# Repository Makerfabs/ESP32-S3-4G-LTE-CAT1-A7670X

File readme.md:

# ESP32-S3-Parallel-TFT-with-Touch-1.9inch

```
/* 
    Version:      V1.0
    Author:       Vincent
    Create Date:  2023/8/22
*/
```

# Makerfabs

[Makerfabs home page](https://www.makerfabs.com/)

[Makerfabs Wiki](https://wiki.makerfabs.com/)

## Intruduce

Product Link:

Wiki Link : 

## Features

- Controller: ESP32-S3
- Wireless: WiFi& Bluetooth 5.0
- Arduino support
- MicroPython support: Yes
- Operation temperature: -40℃ to +85℃
- USB: USB Native, Type-C
- Power Supply: USB Type-C 5.0V(4.0V~5.25V); 3.7V Lipo battery

# Usage

All supporting information, such as the AT instructions and other official documents are in the A76XX Manual.zip.

## Complier Option

- Use type-c use cable connect USB-TTL to PC.
- Select "ESP32-S3 DEV Module"
- Select PSRAM "OPI PSRAM"

## Example

at_command_demo.ino

Serial port transparent transmission demo.
Can be used to test AT Commands.

## AT Commands

### AT+CSQ

Query signal quality

```
AT+CSQ
+CSQ: 28,99

OK

```

### AT+SIMCOMATI

Example Query module information

```
AT+SIMCOMATI
Manufacturer: INCORPORATED
Model: A7670SA-FASE
Revision: A011B04A7670M7_F
A7670M7_B04V02_220927
QCN:
IMEI: 869731059057646
MEID:
+GCAP: +CGSM,+FCLASS,+DS
DeviceInfo:

OK

```

### AT+COPS

Operator selection

```
AT+COPS?
+COPS: 0,2,"46000",7

OK

```

### AT+CICCID

Read ICCID from SIM card

```
AT+CICCID
+ICCID: 898607E0102250030751

OK

```

### AT+CBC

Read the voltage value of the power supply

```
AT+CBC
+CBC: 4.167V

OK

```

## TTS Test

```
AT+CTTSPARAM=? 
AT+CTTSPARAM=1,3,0,1,1 
AT+CTTSPARAM?
AT+CTTS=1,"6B228FCE4F7F75288BED97F3540862107CFB7EDF" 
AT+CTTS=2,"Hi, Makerfabs"

```

## LBS Test

```
AT+CLBS=? 
AT+SIMCOMATI
AT+SIMEI=xxxxx 
AT+CLBS=2 
AT+CLBS=1
```

## Make a call

```
ATD<phone_number>;
AT+COUTGAIN=?
AT+COUTGAIN=5
AT+CHUP 
```
## TCP test

```
AT+CIPMODE=1
AT+NETOPEN
AT+CIPOPEN=0,"TCP","122.114.122.174",39348
Hi,Makerfabs
AT+CIPCLOSE=0
AT+NETCLOSE
```
## LBS Test

```
AT+CLBS=? 
AT+SIMCOMATI
AT+SIMEI=xxxxx 
AT+CLBS=2 
AT+CLBS=1
```
## HTTP Test

```
AT+HTTPINIT
AT+HTTPPARA="URL","http:www.makerfabs.com"
AT+HTTPACTION=0
AT+HTTPHEAD
AT+HTTPREAD=0,500
AT+HTTPTERM
```

## MQTT Test

```
AT+CMQTTSTART
AT+CMQTTACCQ=0,"client test0"
AT+CMQTTWILLTOPIC=0,10
AT+CMQTTWILLMSG=0,6,1
AT+CMQTTCONNECT=0,"tcp://test.mosquitto.org:1883",60,1
AT+CMQTTSUB=0,9,1
AT+CMQTTTOPIC=0,9
AT+CMQTTPAYLOAD=0,60
```

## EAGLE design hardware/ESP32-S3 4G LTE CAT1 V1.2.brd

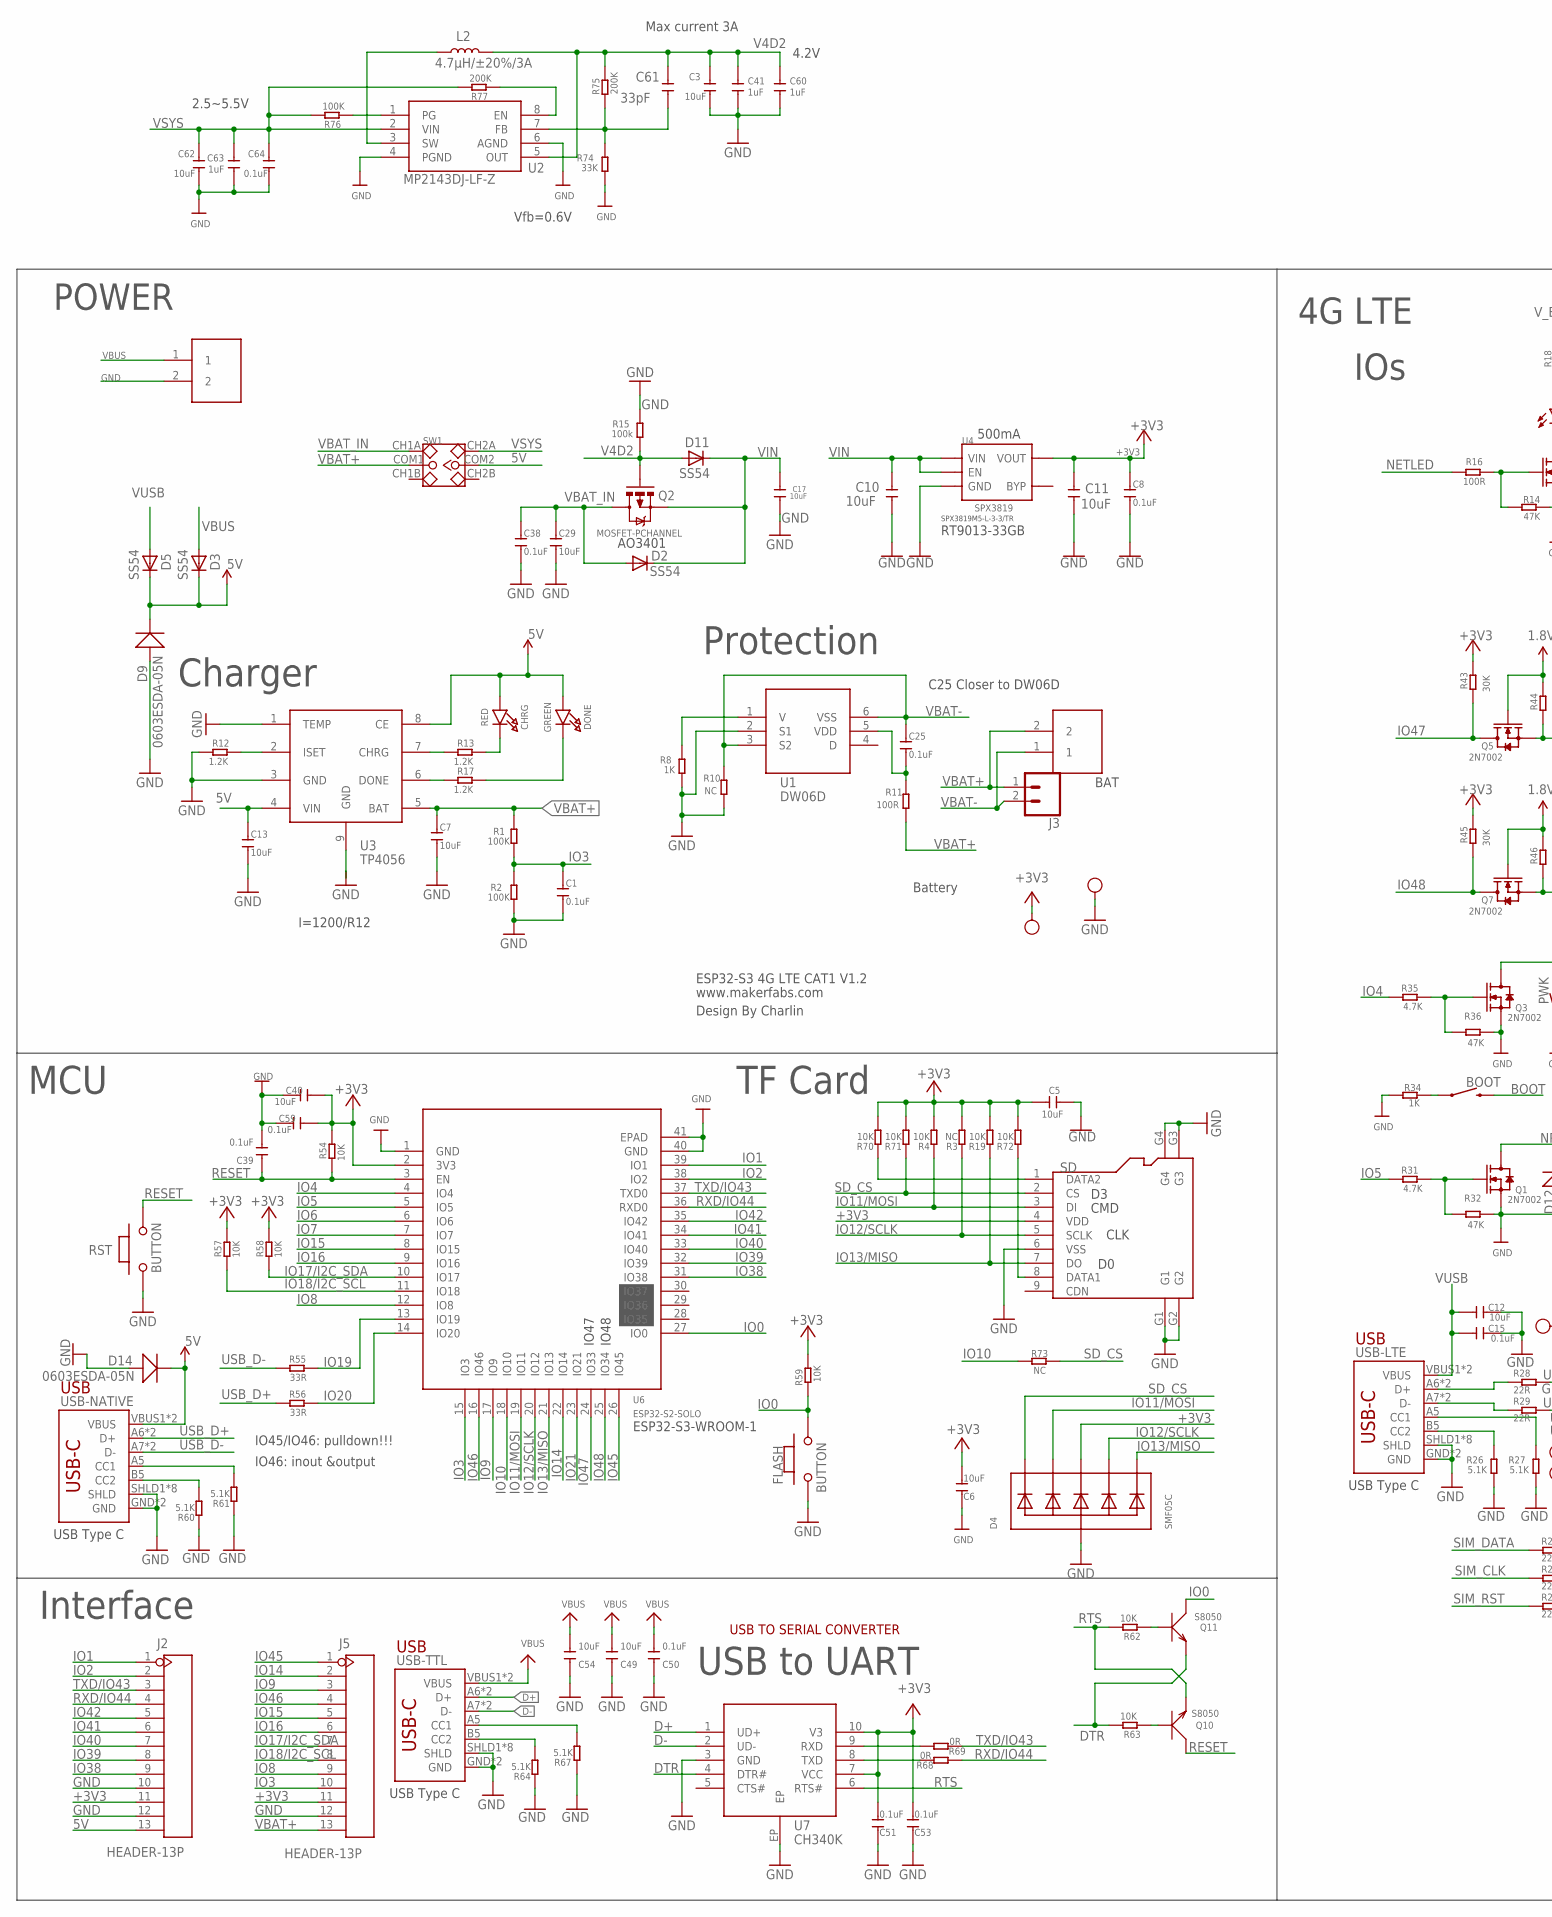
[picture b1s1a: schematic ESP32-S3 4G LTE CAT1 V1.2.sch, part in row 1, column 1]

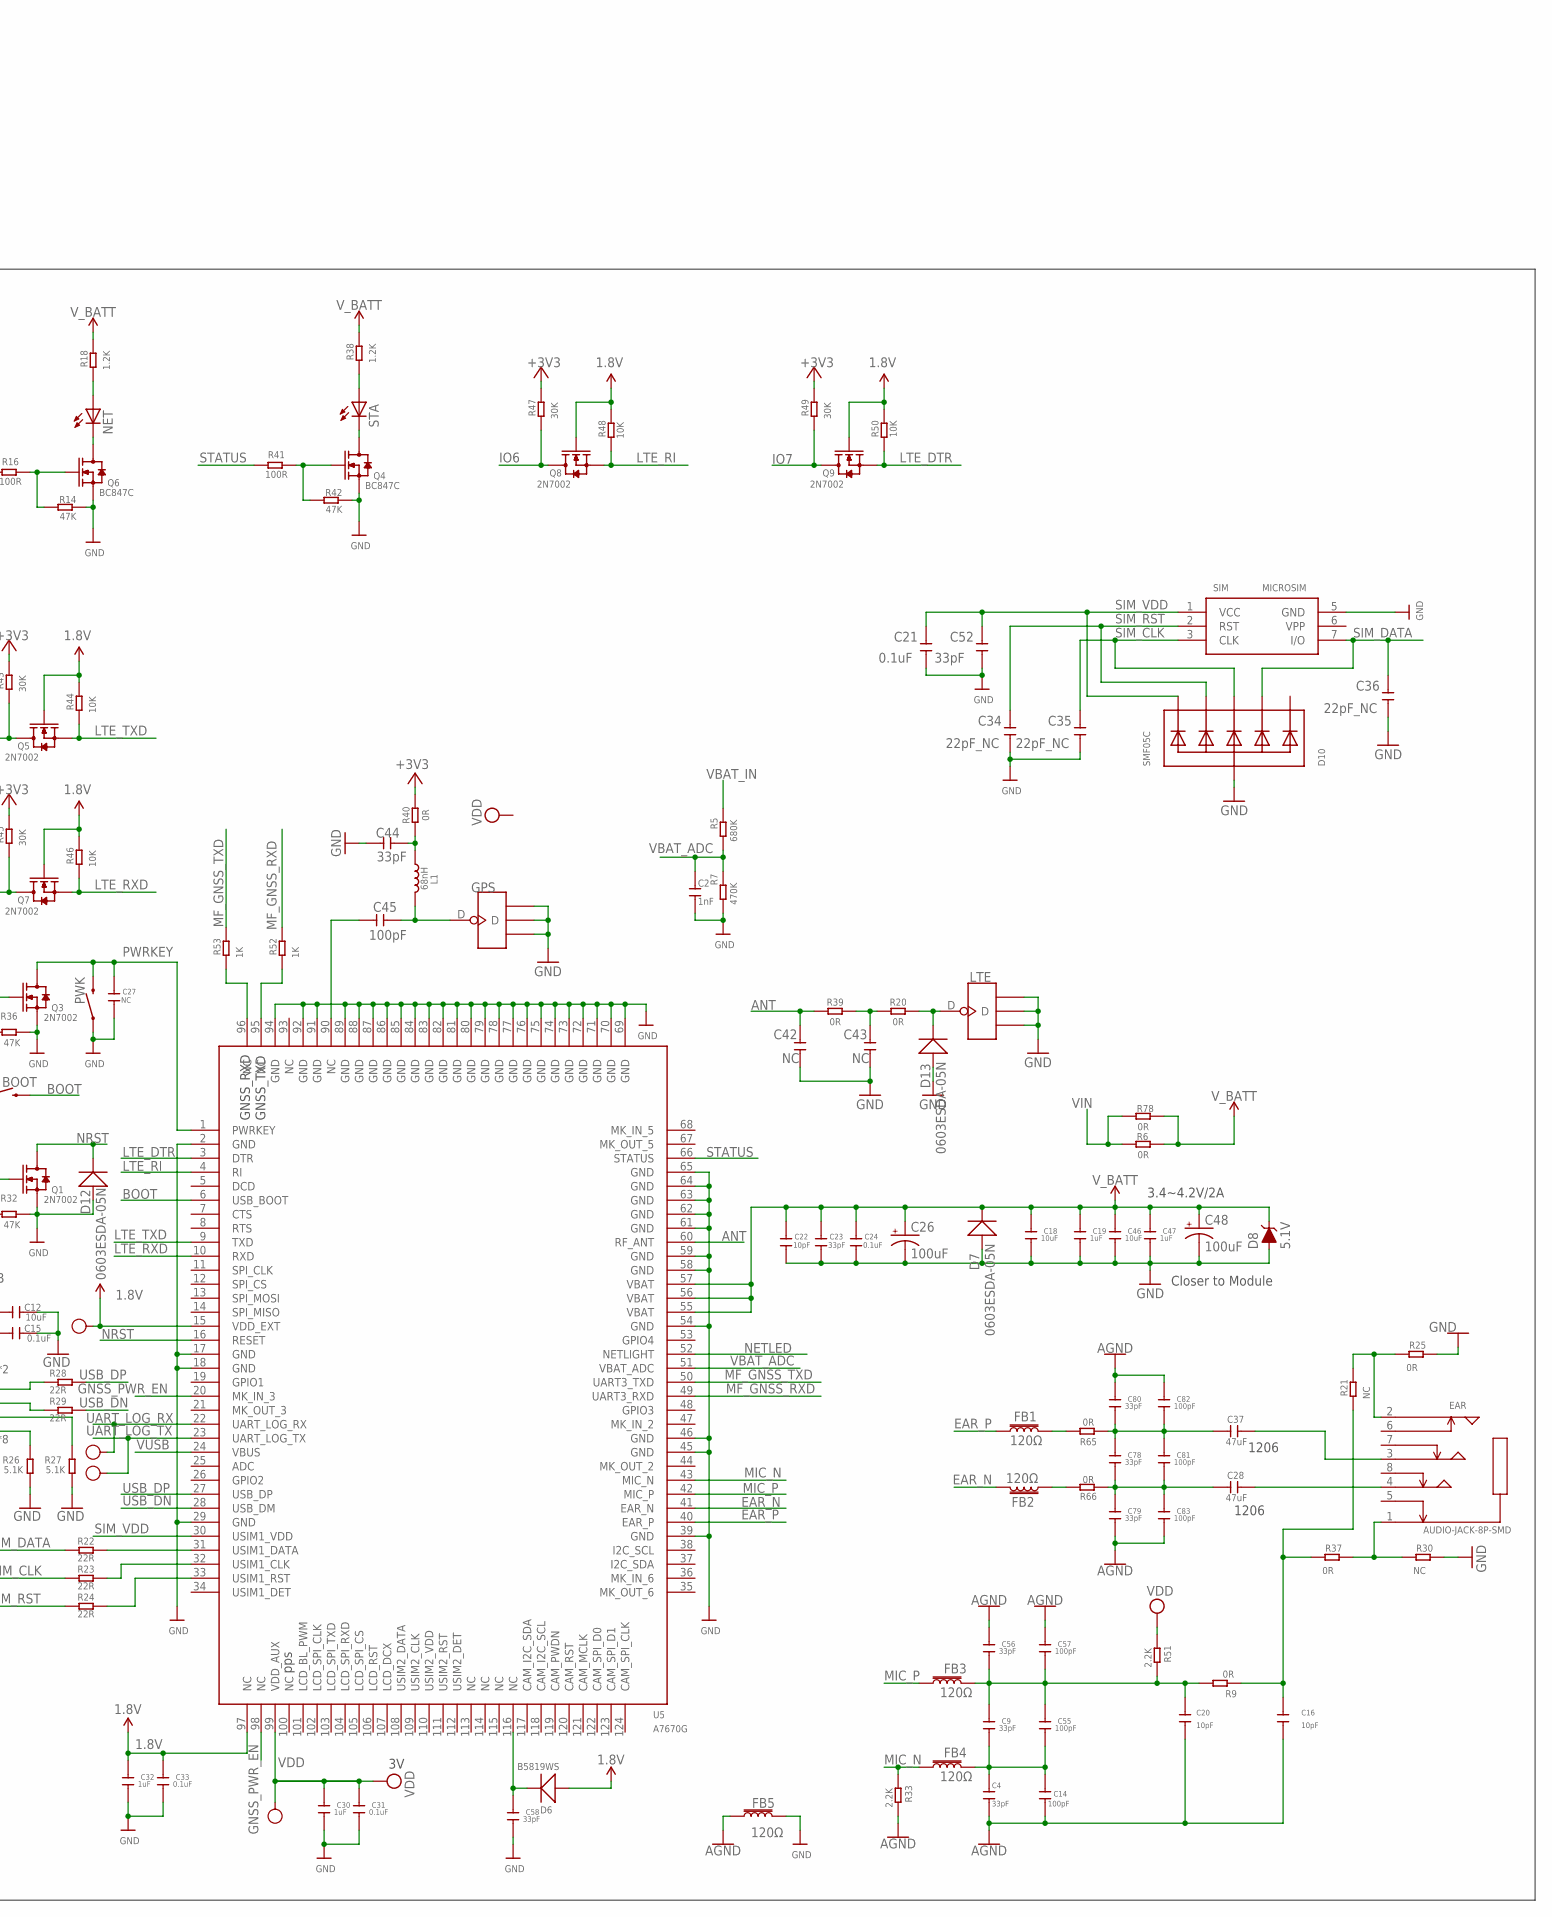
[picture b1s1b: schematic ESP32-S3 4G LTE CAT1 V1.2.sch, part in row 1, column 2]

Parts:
1V8, 3V, 3V3: TEST-POINT'4545'; TP-D45MIL; PARTNO DNP
BAT: PH2.0-2P-90-DIP
BOOT: MOMENTARY-SWITCH-SPST-SMD-6.0X3.5MM; TACTILE_SWITCH_SMD_6.0X3.5MM
C1, C8, C15, C21, C24, C25, C31, C33, C38, C64: 0.1uF; 0603
C2: 1nF; 0603
C3, C7, C10, C11, C12, C13, C17, C18, C29, C46, C62: 10uF; 0603
C4, C9, C23, C44, C52, C56, C58, C61, C78, C79, C80: 33pF; 0603
C5, C6, C40, C49, C54: 10uF; DISCRETE_C0603
C14, C45, C55, C57, C81, C82, C83: 100pF; 0603
C16, C20, C22: 10pF; 0603
C19, C30, C32, C41, C47, C60, C63: 1uF; 0603
C26, C48: 100uF; EIA3528
C27, C42, C43: NC; 0603
C28, C37: 47uF; DISCRETE_C1206
C34, C35, C36: 22pF_NC; 0603
C39, C50, C51, C53, C59: 0.1uF; DISCRETE_C0603
CHRG: RED; CHIPLED_0805_NOOUTLINE
D2, D3, D5, D11: SS54; DO-214AC
D4, D10: SMF05C; SOT363
D6: B5819WS; SOD323
D7, D9, D12, D13, D14: 0603ESDA-05N; DISCRETE_SOD523
D8: 5.1V; SOD-323
DONE: GREEN; CHIPLED_0805_NOOUTLINE
EAR: AUDIO-JACK-8P-SMD; AUDIO8P-SMD-3.5-14.5X6.1X4.0MM
FB1, FB2, FB3, FB4, FB5: 120Ω; 0603
FLASH: BUTTON; 157SW
GND: TEST-POINT'4545'; TP-D45MIL; PARTNO DNP
GPS: ANTENNA-U-FL; 4P-U-FL
J1: PH2.0-2P-90-DIP
J2, J5: HEADER-13P; 13P-2.54
J3: CONN_02LOCK; 1X02_LOCK
L1: 68nH; L0603
L2: 4.7µH/±20%/3A; SRN6045
LTE: ANTENNA-U-FL; 4P-U-FL
NET: NET; CHIP-LED0805
PWK: MOMENTARY-SWITCH-SPST-SMD-6.0X3.5MM; TACTILE_SWITCH_SMD_6.0X3.5MM
Q1, Q3, Q5, Q7, Q8, Q9: 2N7002; SOT23
Q2: MOSFET-PCHANNEL; SOT23-3
Q4, Q6: BC847C; SOT23
Q10, Q11: S8050; SOT23
R1, R2, R76: 100K; R0603
R3: NC; DISCRETE_R0603
R4, R19, R70, R71, R72: 10K; DISCRETE_R0603
R5: 680K; R0603
R6, R9, R20, R25, R37, R39, R40, R65, R66, R68, R69, R78: 0R; R0603
R7: 470K; R0603
R8, R34, R52, R53: 1K; R0603
R10, R21, R30, R73: NC; R0603
R11, R16, R41: 100R; R0603
R12, R13, R17, R18, R38: 1.2K; R0603
R14, R32, R36, R42: 47K; R0603
R15: 100k; R0603
R22, R23, R24, R28, R29: 22R; R0603
R26, R27: 5.1K; R0603
R31, R35: 4.7K; R0603
R33, R51: 2.2K; R0603
R43, R45, R47, R49: 30K; R0603
R44, R46, R48, R50, R54, R57, R58, R59, R62, R63: 10K; R0603
R55, R56: 33R; R0603
R60, R61, R64, R67: 5.1K; DISCRETE_R0603
R74: 33K; R0603
R75, R77: 200K; R0603
RST: BUTTON; 157SW
RX: TEST-POINT'4545'; TP-D45MIL; PARTNO DNP
SD: HOLDER-MICROSD-9P; 9P-SMD-W/-RING
SIM: MICROSIM
STA: NET; CHIP-LED0805
SW1: SWITCH-2CH-6P; 6P-2CH-2.54-7.6X3.0
TX: TEST-POINT'4545'; TP-D45MIL; PARTNO DNP
U1: DW06D; SOT-23-6
U2: MP2143DJ-LF-Z; TSOT23-8
U3: TP4056; SOP8-1.27P
U4: SPX3819; SOT23-5
U5: A7670G
U6: ESP32­S2­SOLO; ESP32-­S2-­SOLO
U7: CH340K; ESOP-10-EP-150MIL
USB-LTE: USB_C5; USB-C-16P-5
USB-NATIVE: USB_C5; USB-C-16P-5
USB-TTL: USB_C5; USB-C-16P-5

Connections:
1.8V: 1V8.T, C32.2, C33.2, D6.+, Q5.1 (G), Q7.1 (G), Q8.1 (G), Q9.1 (G), R44.2, R46.2, R48.2, R50.2, U5.15 (VDD_EXT), U5.97 (NC)
5V: C13.1, CHRG.A, D3.C, D5.C, D9.-, D14.-, DONE.A, J2.13, SW1.COM2, U3.4 (VIN), U3.8 (CE), USB-NATIVE.VBUS1 (VBUS), USB-NATIVE.VBUS2 (VBUS)
+3V3: 3V3.T, C5.2, C6.2, C8.1, C11.2, C40.2, C51.2, C53.2, C59.2, D4.4 (C3), J2.11, J5.11, R3.2, R4.2, R19.2, R40.2, R43.2, R45.2, R47.2, R49.2, R54.2, R57.2, R58.2, R59.2, R70.2, R71.2, R72.2, SD.4 (VDD), U4.5 (VOUT), U6.2 (3V3), U7.7 (VCC), U7.10 (V3)
AGND: C4.1, C14.1, C16.1, C20.1, C56.2, C57.2, C79.1, C80.2, C82.2, C83.1, FB5.1, R33.2
ANT: C42.2, R39.1, U5.60 (RF_ANT)
BOOT: BOOT.2, U5.6 (USB_BOOT)
D+: U7.1 (UD+), USB-TTL.A6 (D+), USB-TTL.B6 (D+)
D-: U7.2 (UD-), USB-TTL.A7 (D-), USB-TTL.B7 (D-)
DONE: R17.2, U3.6 (DONE)
DTR: Q11.2 (E), R63.2, U7.4 (DTR#)
EAR_N: FB2.2, U5.41 (EAR_N)
EAR_P: FB1.1, U5.40 (EAR_P)
GND: C1.2, C2.2, C3.1, C5.1, C6.1, C7.2, C8.2, C10.1, C11.1, C12.2, C13.2, C15.2, C17.1, C18.1, C19.1, C21.1, C22.1, C23.1, C24.1, C26.C (-), C27.1, C29.2, C30.1, C31.1, C32.1, C33.1, C34.1, C35.1, C36.1, C38.2, C39.2, C40.1, C41.1, C42.1, C43.1, C44.2, C46.1, C47.1, C48.C (-), C49.1, C50.1, C51.1, C52.1, C53.1, C54.1, C58.1, C59.1, C60.1, C62.1, C63.1, C64.1, D4.2 (A), D7.+, D8.A, D9.+, D10.2 (A), D12.+, D13.+, D14.+, FB5.2, FLASH.1, GND.T, GPS.GND1, GPS.GND2, GPS.GND3, J1.2, J2.10, J2.12, J5.12, LTE.GND1, LTE.GND2, LTE.GND3, PWK.1, Q1.2 (S), Q3.2 (S), Q4.2 (S), Q6.2 (S), R2.1, R7.1, R8.1, R10.1, R12.2, R14.1, R15.2, R25.2, R26.1, R27.1, R30.2, R32.1, R34.2, R36.1, R42.1, R60.1, R61.1, R64.1, R67.1, R74.1, RST.1, SD.6 (VSS), SD.G1, SD.G2, SD.G3, SD.G4, SIM.5 (GND), U1.2 (S1), U2.4 (PGND), U2.6 (AGND), U3.1 (TEMP), U3.3 (GND), U3.9 (GND), U4.2 (GND), U5.2 (GND), U5.17 (GND), U5.18 (GND), U5.29 (GND), U5.39 (GND), U5.45 (GND), U5.46 (GND), U5.54 (GND), U5.58 (GND), U5.59 (GND), U5.61 (GND), U5.62 (GND), U5.63 (GND), U5.64 (GND), U5.65 (GND), U5.69 (GND), U5.70 (GND), U5.71 (GND), U5.72 (GND), U5.73 (GND), U5.74 (GND), U5.75 (GND), U5.76 (GND), U5.77 (GND), U5.78 (GND), U5.79 (GND), U5.80 (GND), U5.81 (GND), U5.82 (GND), U5.83 (GND), U5.84 (GND), U5.85 (GND), U5.86 (GND), U5.87 (GND), U5.88 (GND), U5.89 (GND), U5.91 (GND), U5.92 (GND), U5.94 (GND), U6.1 (GND), U6.40 (GND), U6.41 (EPAD), U7.3 (GND), U7.EP, USB-LTE.GND, USB-LTE.GND2 (GND), USB-LTE.SHLD1 (SHLD), USB-LTE.SHLD2 (SHLD), USB-LTE.SHLD3 (SHLD), USB-LTE.SHLD4 (SHLD), USB-LTE.SHLD5 (SHLD), USB-LTE.SHLD6 (SHLD), USB-LTE.SHLD7 (SHLD), USB-LTE.SHLD8 (SHLD), USB-NATIVE.GND, USB-NATIVE.GND2 (GND), USB-NATIVE.SHLD1 (SHLD), USB-NATIVE.SHLD2 (SHLD), USB-NATIVE.SHLD3 (SHLD), USB-NATIVE.SHLD4 (SHLD), USB-NATIVE.SHLD5 (SHLD), USB-NATIVE.SHLD6 (SHLD), USB-NATIVE.SHLD7 (SHLD), USB-NATIVE.SHLD8 (SHLD), USB-TTL.GND, USB-TTL.GND2 (GND), USB-TTL.SHLD1 (SHLD), USB-TTL.SHLD2 (SHLD), USB-TTL.SHLD3 (SHLD), USB-TTL.SHLD4 (SHLD), USB-TTL.SHLD5 (SHLD), USB-TTL.SHLD6 (SHLD), USB-TTL.SHLD7 (SHLD), USB-TTL.SHLD8 (SHLD)
GNSS_PWR_EN: U5.20 (MK_IN_3), U5.98 (NC)
IO0: FLASH.2, Q11.3 (C), R59.1, U6.27 (IO0)
IO1: J2.1, U6.39 (IO1)
IO2: J2.2, U6.38 (IO2)
IO3: C1.1, J5.10, R1.1, R2.2, U6.15 (IO3)
IO4: R35.2, U6.4 (IO4)
IO5: R31.2, U6.5 (IO5)
IO6: Q8.3 (D), R47.1, U6.6 (IO6)
IO7: Q9.3 (D), R49.1, U6.7 (IO7)
IO8: J5.9, U6.12 (IO8)
IO9: J5.3, U6.17 (IO9)
IO10: R73.1, U6.18 (IO10)
IO11/MOSI: D4.3 (C2), R4.1, SD.3 (DI), U6.19 (IO11)
IO12/SCLK: D4.5 (C4), R3.1, SD.5 (SCLK), U6.20 (IO12)
IO13/MISO: D4.6 (C5), R19.1, SD.7 (DO), U6.21 (IO13)
IO14: J5.2, U6.22 (IO14)
IO15: J5.5, U6.8 (IO15)
IO16: J5.6, U6.9 (IO16)
IO17/I2C_SDA: J5.7, R58.1, U6.10 (IO17)
IO18/I2C_SCL: J5.8, R57.1, U6.11 (IO18)
IO19: R55.2, U6.13 (IO19)
IO20: R56.2, U6.14 (IO20)
IO21: U6.23 (IO21)
IO38: J2.9, U6.31 (IO38)
IO39: J2.8, U6.32 (IO39)
IO40: J2.7, U6.33 (IO40)
IO41: J2.6, U6.34 (IO41)
IO42: J2.5, U6.35 (IO42)
IO45: J5.1, U6.26 (IO45)
IO46: J5.4, U6.16 (IO46)
IO47: Q5.3 (D), R43.1, U6.24 (IO33)
IO48: Q7.3 (D), R45.1, U6.25 (IO34)
ISET: R12.1, U3.2 (ISET)
LTE_DTR: Q9.2 (S), R50.1, U5.3 (DTR)
LTE_RI: Q8.2 (S), R48.1, U5.4 (RI)
LTE_RXD: Q7.2 (S), R46.1, U5.10 (RXD)
LTE_TXD: Q5.2 (S), R44.1, U5.9 (TXD)
MF_GNSS_RXD: R52.2, U5.49 (UART3_RXD)
MF_GNSS_TXD: R53.2, U5.50 (UART3_TXD)
MIC_N: FB4.1, R33.1, U5.43 (MIC_N)
MIC_P: FB3.1, U5.42 (MIC_P)
unnamed: NET.C, Q6.3 (D)
unnamed: CHRG.C, R13.1
unnamed: D13.-, LTE.D, R20.2
unnamed: Q4.1 (G), R41.1, R42.2
unnamed: Q6.1 (G), R14.2, R16.1
unnamed: NET.A, R18.1
unnamed: R70.1, SD.1 (DATA2)
unnamed: BOOT.1, R34.1
unnamed: C25.2, R11.2, U1.5 (VDD)
unnamed: R8.2, U1.1 (V)
unnamed: DONE.C, R17.1
unnamed: R13.2, U3.7 (CHRG)
unnamed: C16.2, R9.1, R21.1, R37.1
unnamed: C9.2, C20.2, C55.2, C56.1, C57.1, FB3.2, R9.2, R51.2
unnamed: EAR.2, R21.2, R25.1
unnamed: FB2.1, R66.2
unnamed: R72.1, SD.8 (DATA1)
unnamed: C58.2, D6.-, U5.116 (NC)
unnamed: EAR.1, R30.1, R37.2
unnamed: C28.1, C78.1, C79.2, C81.1, C83.2, R66.1
unnamed: R22.1, U5.31 (USIM1_DATA)
unnamed: R23.1, U5.32 (USIM1_CLK)
unnamed: R24.1, U5.33 (USIM1_RST)
unnamed: C4.2, C9.1, C14.2, C55.1, FB4.2
unnamed: L2.1, U2.3 (SW)
unnamed: R27.2, USB-LTE.A5 (CC1)
unnamed: R26.2, USB-LTE.B5 (CC2)
unnamed: R38.1, STA.A
unnamed: Q4.3 (D), STA.C
unnamed: C37.1, C78.2, C80.1, C81.2, C82.1, R65.1
unnamed: R28.2, USB-LTE.A6 (D+), USB-LTE.B6 (D+)
unnamed: R29.2, USB-LTE.A7 (D-), USB-LTE.B7 (D-)
unnamed: Q1.1 (G), R31.1, R32.2
unnamed: C45.2, U5.90 (NC)
unnamed: C28.2, EAR.4
unnamed: R52.1, U5.95 (NC)
unnamed: R53.1, U5.96 (NC)
unnamed: C61.1, R74.2, R75.1, U2.7 (FB)
unnamed: R76.1, U2.1 (PG)
unnamed: R61.2, USB-NATIVE.A5 (CC1)
unnamed: R60.2, USB-NATIVE.B5 (CC2)
unnamed: Q3.1 (G), R35.1, R36.2
unnamed: Q10.1 (B), R63.1
unnamed: Q11.1 (B), R62.1
unnamed: R67.2, USB-TTL.A5 (CC1)
unnamed: R64.2, USB-TTL.B5 (CC2)
unnamed: R69.2, U7.9 (RXD)
unnamed: R68.2, U7.8 (TXD)
unnamed: R77.1, U2.8 (EN)
unnamed: FB1.2, R65.2
unnamed: C37.2, EAR.3
unnamed: C43.2, R20.1, R39.2
unnamed: C44.1, L1.1, R40.1
unnamed: C45.1, GPS.D, L1.2
NETLED: R16.2, U5.52 (NETLIGHT)
NRST: D12.-, Q1.3 (D), U5.16 (RESET)
PWRKEY: C27.2, PWK.2, Q3.3 (D), U5.1 (PWRKEY)
RESET: C39.1, Q10.3 (C), R54.1, RST.2, U6.3 (EN)
RTS: Q10.2 (E), R62.2, U7.6 (RTS#)
RXD/IO44: J2.4, R68.1, U6.36 (RXD0)
SD_CS: D4.1 (C1), R71.1, R73.2, SD.2 (CS)
SIM_CLK: C35.2, D10.4 (C3), R23.2, SIM.3 (CLK)
SIM_DATA: C36.2, D10.3 (C2), R22.2, SIM.7 (I/O)
SIM_RST: C34.2, D10.5 (C4), R24.2, SIM.2 (RST)
SIM_VDD: C21.2, C52.2, D10.6 (C5), SIM.1 (VCC), U5.30 (USIM1_VDD)
STATUS: R41.2, U5.66 (STATUS)
TXD/IO43: J2.3, R69.1, U6.37 (TXD0)
UART_LOG_RX: RX.T, U5.22 (UART_LOG_RX)
UART_LOG_TX: TX.T, U5.23 (UART_LOG_TX)
USB_D+: R56.1, USB-NATIVE.A6 (D+), USB-NATIVE.B6 (D+)
USB_D-: R55.1, USB-NATIVE.A7 (D-), USB-NATIVE.B7 (D-)
USB_DN: R29.1, U5.28 (USB_DM)
USB_DP: R28.1, U5.27 (USB_DP)
V4D2: C3.2, C41.2, C60.2, C61.2, D11.A, L2.2, Q2.1 (G), R15.1, R75.2, U2.5 (OUT)
VBAT+: BAT.2, C7.1, J3.1, J5.13, R1.2, R11.1, SW1.COM1, U3.5 (BAT)
VBAT-: BAT.1, C25.1, J3.2, R10.2, U1.3 (S2), U1.6 (VSS)
VBAT_ADC: C2.1, R5.1, R7.2, U5.51 (VBAT_ADC)
VBAT_IN: C29.1, C38.1, D2.A, Q2.3 (D), R5.2, SW1.CH1A
VBUS: C49.2, C50.2, C54.2, D3.A, J1.1, USB-TTL.VBUS1 (VBUS), USB-TTL.VBUS2 (VBUS)
VDD: 3V.T, C30.2, C31.2, R51.1, U5.99 (VDD_AUX)
VIN: C10.2, C17.2, D2.C, D11.C, Q2.2 (S), R6.2, R78.2, U4.1 (VIN), U4.3 (EN)
VSYS: C62.2, C63.2, C64.2, R76.2, R77.2, SW1.CH2A, U2.2 (VIN)
VUSB: C12.1, C15.1, D5.A, U5.24 (VBUS), USB-LTE.VBUS1 (VBUS), USB-LTE.VBUS2 (VBUS)
V_BATT: C18.2, C19.2, C22.2, C23.2, C24.2, C26.A (+), C46.2, C47.2, C48.A (+), D7.-, D8.C, R6.1, R18.2, R38.2, R78.1, U5.55 (VBAT), U5.56 (VBAT), U5.57 (VBAT)

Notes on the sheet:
ESP32-S3 4G LTE CAT1 V1.2
www.makerfabs.com
IOs
Battery
C25 Closer to DW06D
Protection
BAT
I=1200/R12
Charger
500mA
POWER
AO3401
SPX3819M5-L-3-3/TR
RT9013-33GB
USB
USB Type C
Closer to Module
3.4~4.2V/2A
GNSS_TXD
GNSS_RXD
1206
IO45/IO46: pulldown!!!
IO46: inout &output
MCU
ESP32-S3-WROOM-1
IO47
IO48
USB TO SERIAL CONVERTER
USB to UART
Design By Charlin
TF Card
CMD
CLK
4G LTE
Interface
pps
4.2V
Max current 3A
Vfb=0.6V
2.5~5.5V

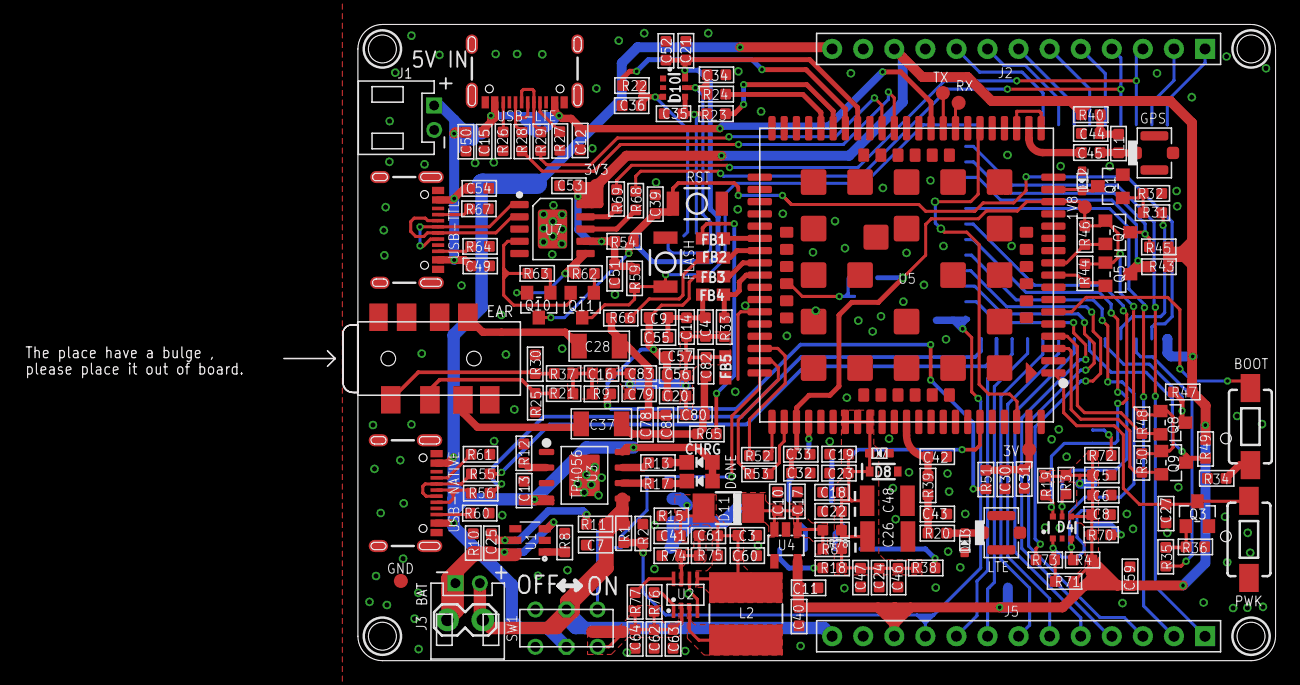
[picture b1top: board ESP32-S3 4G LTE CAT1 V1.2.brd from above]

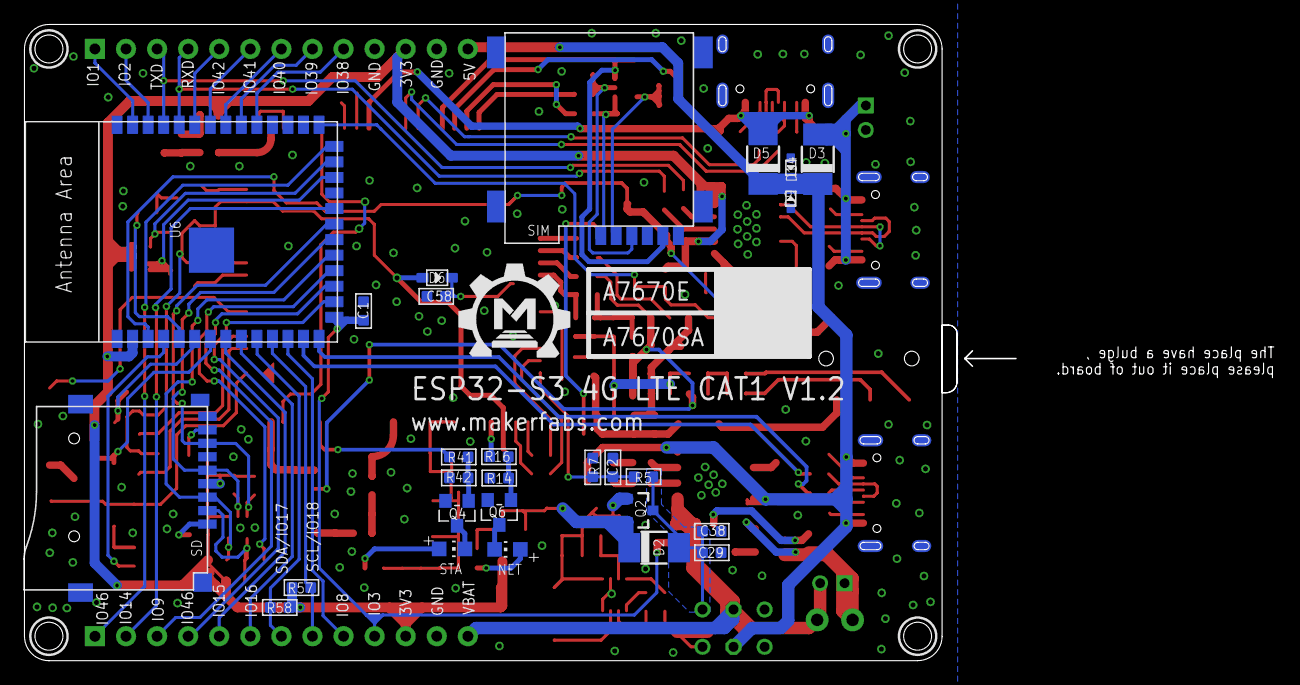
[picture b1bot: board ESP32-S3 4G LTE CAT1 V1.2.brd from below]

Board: 2 copper layers, 81.0 x 52.0 mm, 215 parts (28 on the bottom side), 137 nets.

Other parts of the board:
U$1: MAKERFABS_0.3

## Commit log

2023-08-22 Create
2024-02-18 Add schematic of PDF
2024-02-19 Update hardware
2026-06-12 Add sch and brd

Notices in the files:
parts and their libraries:
microbuilder: This work is placed in the public domain, and may be freely used for commercial and non-commercial work with the following conditions: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
SparkFun-Connectors: Licensing: Creative Commons ShareAlike 4.0 International - https://creativecommons.org/licenses/by-sa/4.0
